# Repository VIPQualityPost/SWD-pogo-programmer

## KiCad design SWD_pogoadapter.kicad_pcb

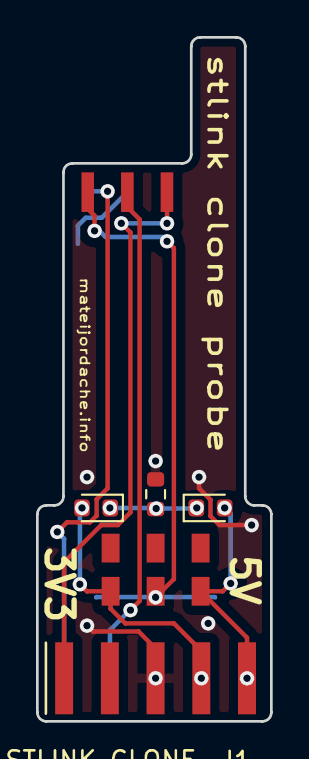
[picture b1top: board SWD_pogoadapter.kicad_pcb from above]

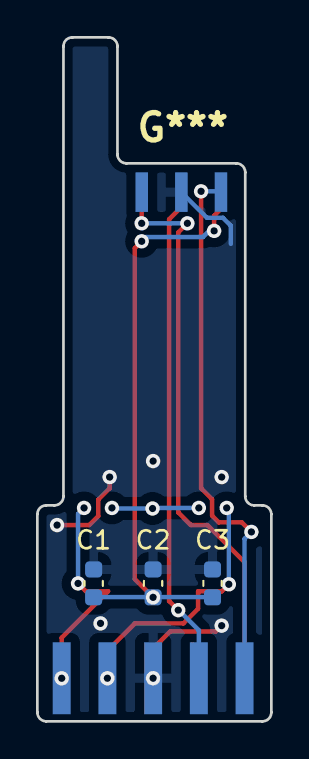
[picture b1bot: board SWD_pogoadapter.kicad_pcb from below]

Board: 2 copper layers, 13.0 x 38.0 mm, 9 parts (3 on the bottom side), 8 nets.

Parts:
C1: .1uF; C_0603_1608Metric
C2: 1uF; C_0603_1608Metric
C3: 10uF; C_0603_1608Metric
D1: 5V; D_0603_1608Metric
D2: 3V3; D_0603_1608Metric
J1: STLINK CLONE; 02x05_sidemount
J2: POGO; SWD_pogo_combined
R1: 10k; R_0603_1608Metric
SW1: SW_Push_DPDT; JS202011JCQN

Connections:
3V3: D2.2 (A), J1.4, J1.7, SW1.1 (A)
5V: D1.2 (A), J1.5, J1.6, SW1.3 (C)
GND: C1.2, C2.2, C3.2, J1.3, J1.8, J2.5, R1.2
NRESET: J1.1, J2.3
unnamed: D1.1 (K), D2.1 (K), R1.1
SUPPLYV: C1.1, C2.1, C3.1, J2.1, SW1.2 (B)
SWCLK: J1.10, J2.6
SWDIO: J1.9, J2.2

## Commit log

2022-11-18 initial files
2023-02-13 Auto-commit Mon Feb 13 12:20:14 EST 2023
2023-02-17 Auto-commit Thu Feb 16 21:35:03 EST 2023
2023-02-17 Auto-commit Fri Feb 17 12:27:52 EST 2023
2023-02-17 Auto-commit Fri Feb 17 13:04:09 EST 2023
2023-02-17 Remove ignored files
